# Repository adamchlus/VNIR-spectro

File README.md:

# VNIR-spectro

This repository contains code, schematics and 3d models for building a lowcost, handheld visible near-infrared spectrometer.

For more information check out:

https://hackaday.io/project/12724-handheld-vnir-spectrometer

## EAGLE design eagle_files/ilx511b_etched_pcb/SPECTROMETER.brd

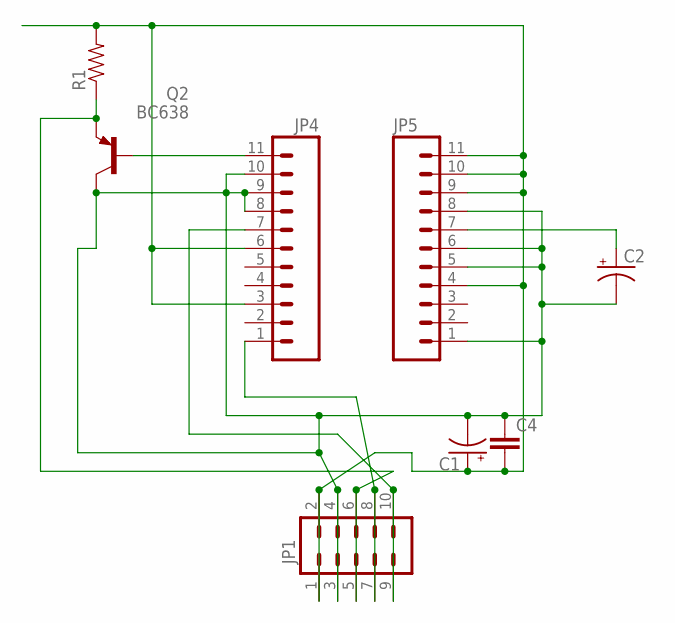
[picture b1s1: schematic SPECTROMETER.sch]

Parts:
C1, C2: CAP_POLPTH1; CPOL-RADIAL-100UF-25V
C4: CAPPTH1; CAP-PTH-5MM
JP1: M05X2NO_SILK; 2X5_NOSILK
JP4, JP5: M11LOCK; 1X11_LOCK
Q2: BC638; TO92-BCE
R1: RESISTORKIT; AXIAL-0.3-KIT

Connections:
unnamed: JP1.9, JP1.10, JP4.7
unnamed: C1.1 (+), C4.2, JP1.1, JP1.2, JP4.3, JP4.6, JP5.4, JP5.9, JP5.10, JP5.11, R1.P$2 (2)
unnamed: C2.1 (+), JP5.7
unnamed: JP1.5, JP1.6, Q2.E, R1.P$1 (1)
unnamed: JP4.11, Q2.B
unnamed: JP1.7, JP1.8, JP4.1
unnamed: C1.2 (-), C2.2 (-), C4.1, JP1.3, JP1.4, JP4.8, JP4.9, JP4.10, JP5.1, JP5.5, JP5.6, JP5.8, Q2.C

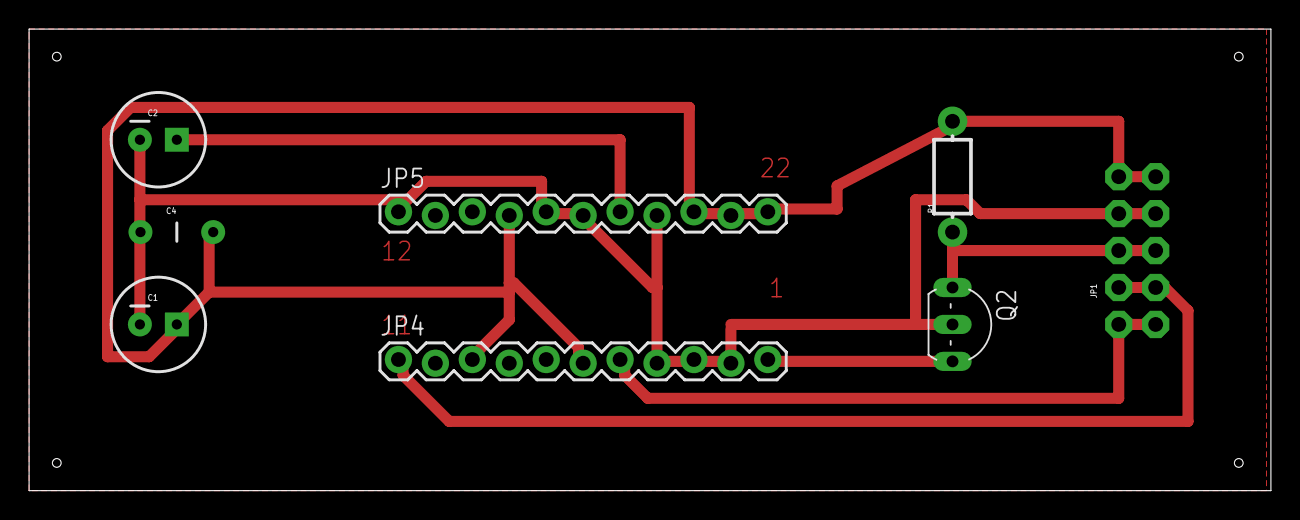
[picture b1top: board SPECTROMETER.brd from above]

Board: 2 copper layers, 85.4 x 31.7 mm, 8 parts (0 on the bottom side), 7 nets.

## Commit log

2016-10-23 added ILX511 CCD controller code
2016-10-23 added screenshot from oscilloscope
2016-10-24 update code comments
2016-10-24 added eagle files for etched ILX511 pcb

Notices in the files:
parts and their libraries:
SparkFun-Capacitors: Licensing: Creative Commons ShareAlike 4.0 International - https://creativecommons.org/licenses/by-sa/4.0
